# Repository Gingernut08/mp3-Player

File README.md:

MP3 player shaped and sized like a cassette tape, up to 300 songs, 5 control buttons and a 500mah battery with integrated usbc charger

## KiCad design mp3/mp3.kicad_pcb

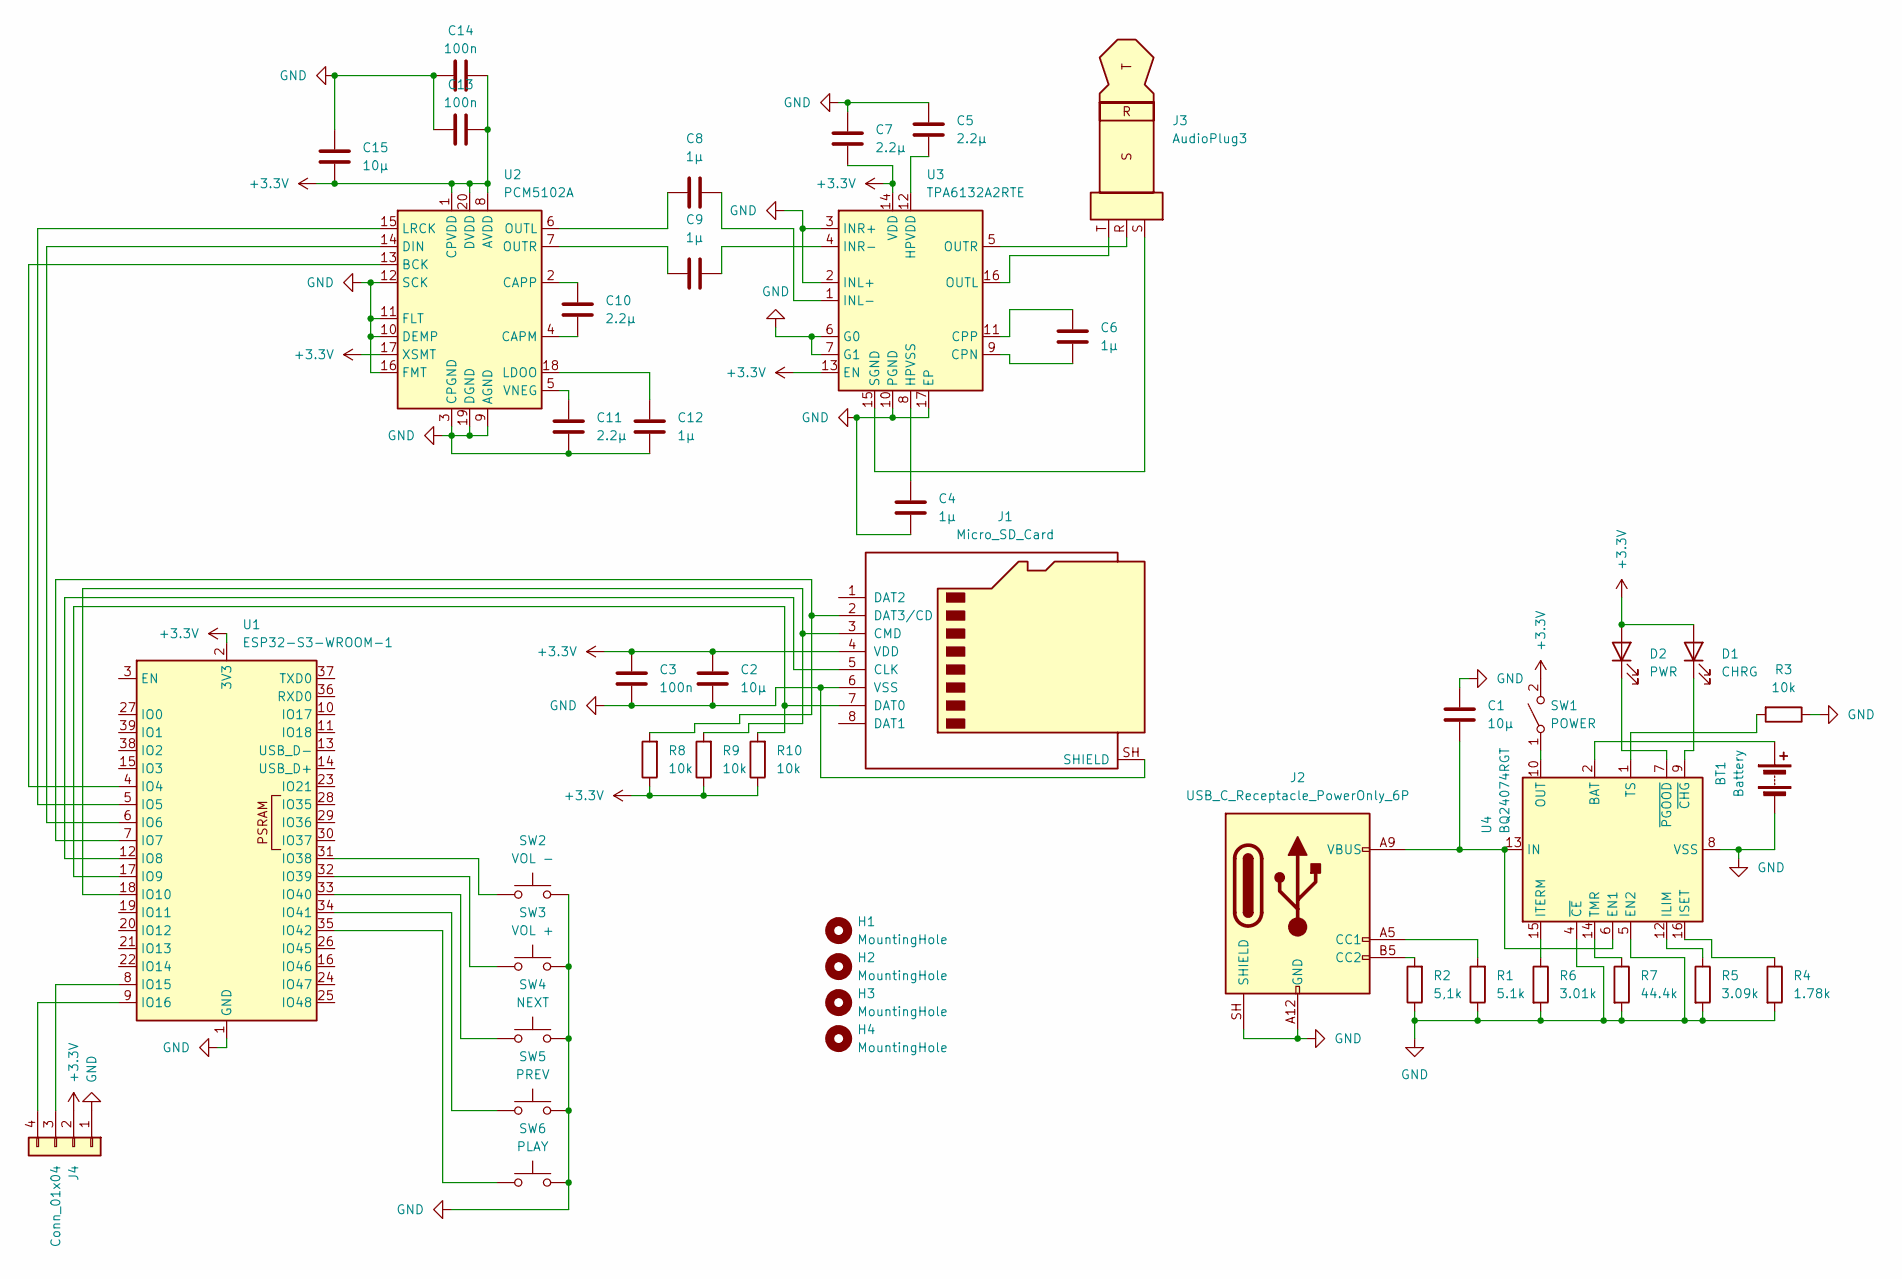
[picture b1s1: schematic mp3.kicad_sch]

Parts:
BT1: Battery
C1, C2, C15: 10μ; C_0805_2012Metric
C3, C13, C14: 100n; C_0603_1608Metric
C4, C6, C8, C9, C12: 1μ; C_0603_1608Metric
C5, C7, C10, C11: 2.2μ; C_0805_2012Metric
D1: CHRG; Switch
D2: PWR; Switch
H1, H2, H3, H4: MountingHole; MountingHole_2.2mm_M2
J1: Micro_SD_Card
J2: USB_C_Receptacle_PowerOnly_6P
J3: AudioPlug3; AudioJack3
J4: Conn_01x04; OLED
R1: 5.1k; R_0603_1608Metric
R2: 5,1k; R_0603_1608Metric
R3, R8, R9, R10: 10k; R_0603_1608Metric
R4: 1.78k; R_0603_1608Metric
R5: 3.09k; R_0603_1608Metric
R6: 3.01k; R_0603_1608Metric
R7: 44.4k; R_0603_1608Metric
SW1: POWER; Switch
SW2: VOL -; Switch
SW3: VOL +; Switch
SW4: NEXT; Switch
SW5: PREV; Switch
SW6: PLAY; Switch
U1: ESP32-S3-WROOM-1
U2: PCM5102A; TSSOP-20_4.4x6.5mm_P0.65mm
U3: TPA6132A2RTE; WQFN-16-1EP_3x3mm_P0.5mm_EP1.6x1.6mm_ThermalVias
U4: BQ24074RGT; VQFN-16-1EP_3x3mm_P0.5mm_EP1.6x1.6mm

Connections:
+3.3V: C2.1, C3.1, C7.2, C13.1, C14.1, C15.2, D1.2 (A), D2.2 (A), J1.4 (VDD), J4.2, R8.1, R9.1, R10.1, SW1.2 (B), U1.2 (3V3), U2.1 (CPVDD), U2.8 (AVDD), U2.17 (XSMT), U2.20 (DVDD), U3.13 (EN), U3.14 (VDD); also elsewhere on the board
GND: BT1.2 (-), C1.1, C2.2, C3.2, C4.2, C5.1, C7.1, C11.1, C12.1, C13.2, C14.2, C15.1, J1.6 (VSS), J1.SH (SHIELD), J2.A12 (GND), J2.B12 (GND), J2.SH (SHIELD), J4.1, R1.1, R2.1, R3.1, R4.2, R5.2, R6.2, R7.2, SW2.2, SW3.2, SW4.2, SW5.2, SW6.2, U1.1 (GND), U1.40 (GND), U1.41 (GND), U2.3 (CPGND), U2.9 (AGND), U2.10 (DEMP), U2.11 (FLT), U2.12 (SCK), U2.16 (FMT), U2.19 (DGND), U3.2 (INL+), U3.3 (INR+), U3.6 (G0), U3.7 (G1), U3.10 (PGND), U3.17 (EP), U4.4 (~CE), U4.5 (EN2), U4.8 (VSS), U4.17 (VSS); also elsewhere on the board
unnamed: BT1.1 (+), U4.2 (BAT), U4.3 (BAT)
unnamed: D1.1 (K), U4.9 (~CHG)
unnamed: D2.1 (K), U4.7 (~PGOOD)
unnamed: J1.5 (CLK), U1.12 (IO8)
unnamed: J1.3 (CMD), R9.2, U1.18 (IO10)
unnamed: J1.7 (DAT0), R10.2, U1.17 (IO9)
unnamed: J1.2 (DAT3/CD), R8.2, U1.7 (IO7)
unnamed: J2.A5 (CC1), R1.2
unnamed: J2.B5 (CC2), R2.2
unnamed: J4.3, U1.8 (IO15)
unnamed: J4.4, U1.9 (IO16)
unnamed: SW1.1 (A), U4.10 (OUT), U4.11 (OUT)
unnamed: U1.4 (IO4), U2.13 (BCK)
unnamed: U1.5 (IO5), U2.15 (LRCK)
unnamed: U1.6 (IO6), U2.14 (DIN)
unnamed: SW2.1, U1.31 (IO38)
unnamed: SW3.1, U1.32 (IO39)
unnamed: SW4.1, U1.33 (IO40)
unnamed: SW5.1, U1.34 (IO41)
unnamed: SW6.1, U1.35 (IO42)
unnamed: C10.1, U2.4 (CAPM)
unnamed: C10.2, U2.2 (CAPP)
unnamed: C12.2, U2.18 (LDOO)
unnamed: C8.1, U2.6 (OUTL)
unnamed: C9.1, U2.7 (OUTR)
unnamed: C11.2, U2.5 (VNEG)
unnamed: C6.2, U3.9 (CPN)
unnamed: C6.1, U3.11 (CPP)
unnamed: C5.2, U3.12 (HPVDD)
unnamed: C4.1, U3.8 (HPVSS)
unnamed: C8.2, U3.1 (INL-)
unnamed: C9.2, U3.4 (INR-)
unnamed: J3.T, U3.16 (OUTL)
unnamed: J3.R, U3.5 (OUTR)
unnamed: J3.S, U3.15 (SGND)
unnamed: C1.2, J2.A9 (VBUS), J2.B9 (VBUS), U4.6 (EN1), U4.13 (IN)
unnamed: R5.1, U4.12 (ILIM)
unnamed: R4.1, U4.16 (ISET)
unnamed: R6.1, U4.15 (ITERM)
unnamed: R7.1, U4.14 (TMR)
unnamed: R3.2, U4.1 (TS)

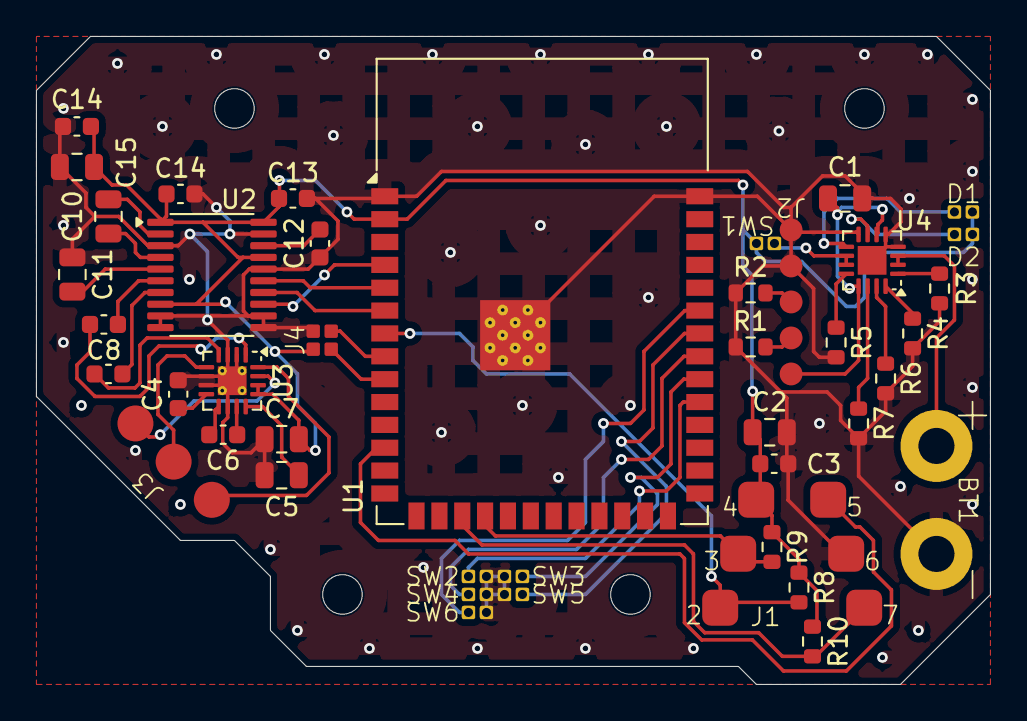
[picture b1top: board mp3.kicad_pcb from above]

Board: 2 copper layers, 53.0 x 36.0 mm, 47 parts (0 on the bottom side), 43 nets.

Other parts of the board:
C14#2: 100n; C_0603_1608Metric

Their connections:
+3.3V: C14#2.1; also elsewhere on the board
GND: C14#2.2; also elsewhere on the board
